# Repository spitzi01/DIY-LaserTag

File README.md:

# ESP32-LaserTag
Easy Open Source LaserTag System
### Überblick
Ziel dieses Projektes war der Bau eines einfachen LaserTag-Systems. Es sollte schnell und mit wenig Hardware an beliebigen Orten aufbaubar sein und  und über ein Handy gesteuert werden können.

Weitere Features sind:

- Soundausgabe für Schuss, Treffer und Nachladen (insgesamt 5 Verschiedene)
- Display in jedem Tagger
- lange Akkulaufzeit des gesamten Systems
- 3 Spielmodi
- Taschenlampe
- rote Laserdiode für Schuss-Simulation
- 5 in den Tagger integriete Infrarot-Empfänger
    
Das LaserTag-System besteht aus zwei elementaren Bestandteilen. Die Basisstation dient als Verbindungsglied zwischen den Taggern, der einzelnen Spieler, und einer HTTP-Website, welche der Konfiguration und Auswertung dient. Der Datenaustausch mit den Spielern erfolgt drahtlos mit Hilfe des EspNow-Protokolls der ESP32 S2 Mikrocontroller. Zum Spielen sind zwischen 2 und 10 Tagger notwendig. Für den Capture the Flag Spielmodus werden zusätzlich noch Flags benötigt, die die Basis und Spawnpunkt eines Team markieren.

### Basisstation

Nach dem Einschalten der Basisstation wird ein WLAN-Netzwerk erzeugt und die Konfigurationswebsite gehostet. Wenn man sich hier mit einem Smartphone einloggt, kann man die Anzahl der Spieler, Dauer des Spiels, Modus, Namen der Spieler und Teamzugehörigkeit einstellen. Die maximal 10 Spieler können auf 6 Teams verteilt werden. Vor dem Starten des Spiels mit dem Start-Taster müssen unbedingt alle Tagger, die verwendet werden sollen, eingeschaltet werden, damit diese von der Basisstation ihre Informationen erhalten können. Nach Ablauf der Spieldauer übermitteln die Tagger automatisch die Spielstände an die Basisstation und schalten sich ab. Die Basisstation berechnet die Ergebnisse und hostet diese in Form einer Website. Das hat den Vorteil, dass sich theoretisch mehrere Spieler die Ergebnisse auf ihren Smartphones anschauen können.

### Tagger

Bei einem Testsystem wurde festgestellt, dass es dem Spieler nicht möglich sein darf, seinen Tagger aus Versehen auszuschalten. Deshalb wird die Schaltung durch einen Taster aktiviert und nur durch den Mikrocontroller wieder deaktiviert. Außerdem soll der Spieler immer beide Hände am Tagger haben. So soll verhindert werden, dass man mit einer Hand Sensoren abdecken könnte. Dies wird durch einen Taster in Reihe zum eigentlichen Abzug realisiert. Gleichzeitig schaltet dieser auch die Taschenlampe an. In meinem Fall dient ein kleiner 12V Bleiakku aus einer Brandmeldezentrale als Energieversorgung. Mit Hilfe des Step Down Converters wird eine hohe Effizienz und Akkulaufzeit erreicht. Das Display hat 20 alphanumerische Stellen, welche die Namen der Spieler und die Anzahl der Leben anzeigen. Eine Hintergrundbeleuchtung ist nicht vorhanden, da diese zu viel Strom benötigen würde. Deshalb dient die RGB-LED für die Teamzugehörigkeit als Beleuchtung. Edit: Mittlerweile wurde das Display durch ein OLED 0,96" Display getauscht, da das LCD Display nicht mehr verfügbar war. Ebenso wurde der Akku durch einen günstigen 12V Lithium-Ionen Akku ersetzt.

Der Schuss wird durch eine Laserdiode visualisiert. Die eigentliche Information findet durch eine IR-Übertragung ihren Weg zu anderen Spielern. Bei Tests in der Nacht konnte eine Reichweite von bis zu 60 Meter erzielt werden. Der kurze Alu-Lauf dient als Reflektor für die Infrarot-LED und auch als Kühlkörper, da bei aktiviertem Schnellfeuermodus die LED sehr belastet wird.

Die verfügbaren Spielmodi sind:

- Standard (Spielen in Teams oder Einzeln, Reaktivierung nach ca. 20 Sekunden)
- Battle Royal (Spielen in Teams oder Einzeln, Leben werden bei Treffer weniger, kein Treffer in gewisser Zeit fügt ein Leben hinzu, lange Reaktivierungszeit ca. 2 Minuten)
- Capture the Flag (2 Teams rot & blau, Flags markieren Basis oder Spawnpunkt des jeweiligen Teams, Reaktivierung nur im Bereich des eigenen Spawnpunkts, Punkte bei Aufenthalt in gegnerischen Basis)

### Flag
Ein Flag sendet in regelmäßigen Abständen einen Code der von den Taggern empfangen wird. Bereich, in dem das Signal empfangbar ist, beträgt in etwa 5-8 Meter im Radius. Diese Strecke ergibt sich durch den Einsatz von ESP32 S2 Mikrocontroller ohne integriete Antenne in den Taggern.

### Verbesserungsmöglichkeiten

- Reichweite bei starkem Sonnenschein eingeschränkt
- Mikrocontroller überträgt kurzes Störgeräusch über I2S nach Ende einer Soundausgabe (Software Problem)
- Skalierbarkeit (mehr als 10 Spieler)

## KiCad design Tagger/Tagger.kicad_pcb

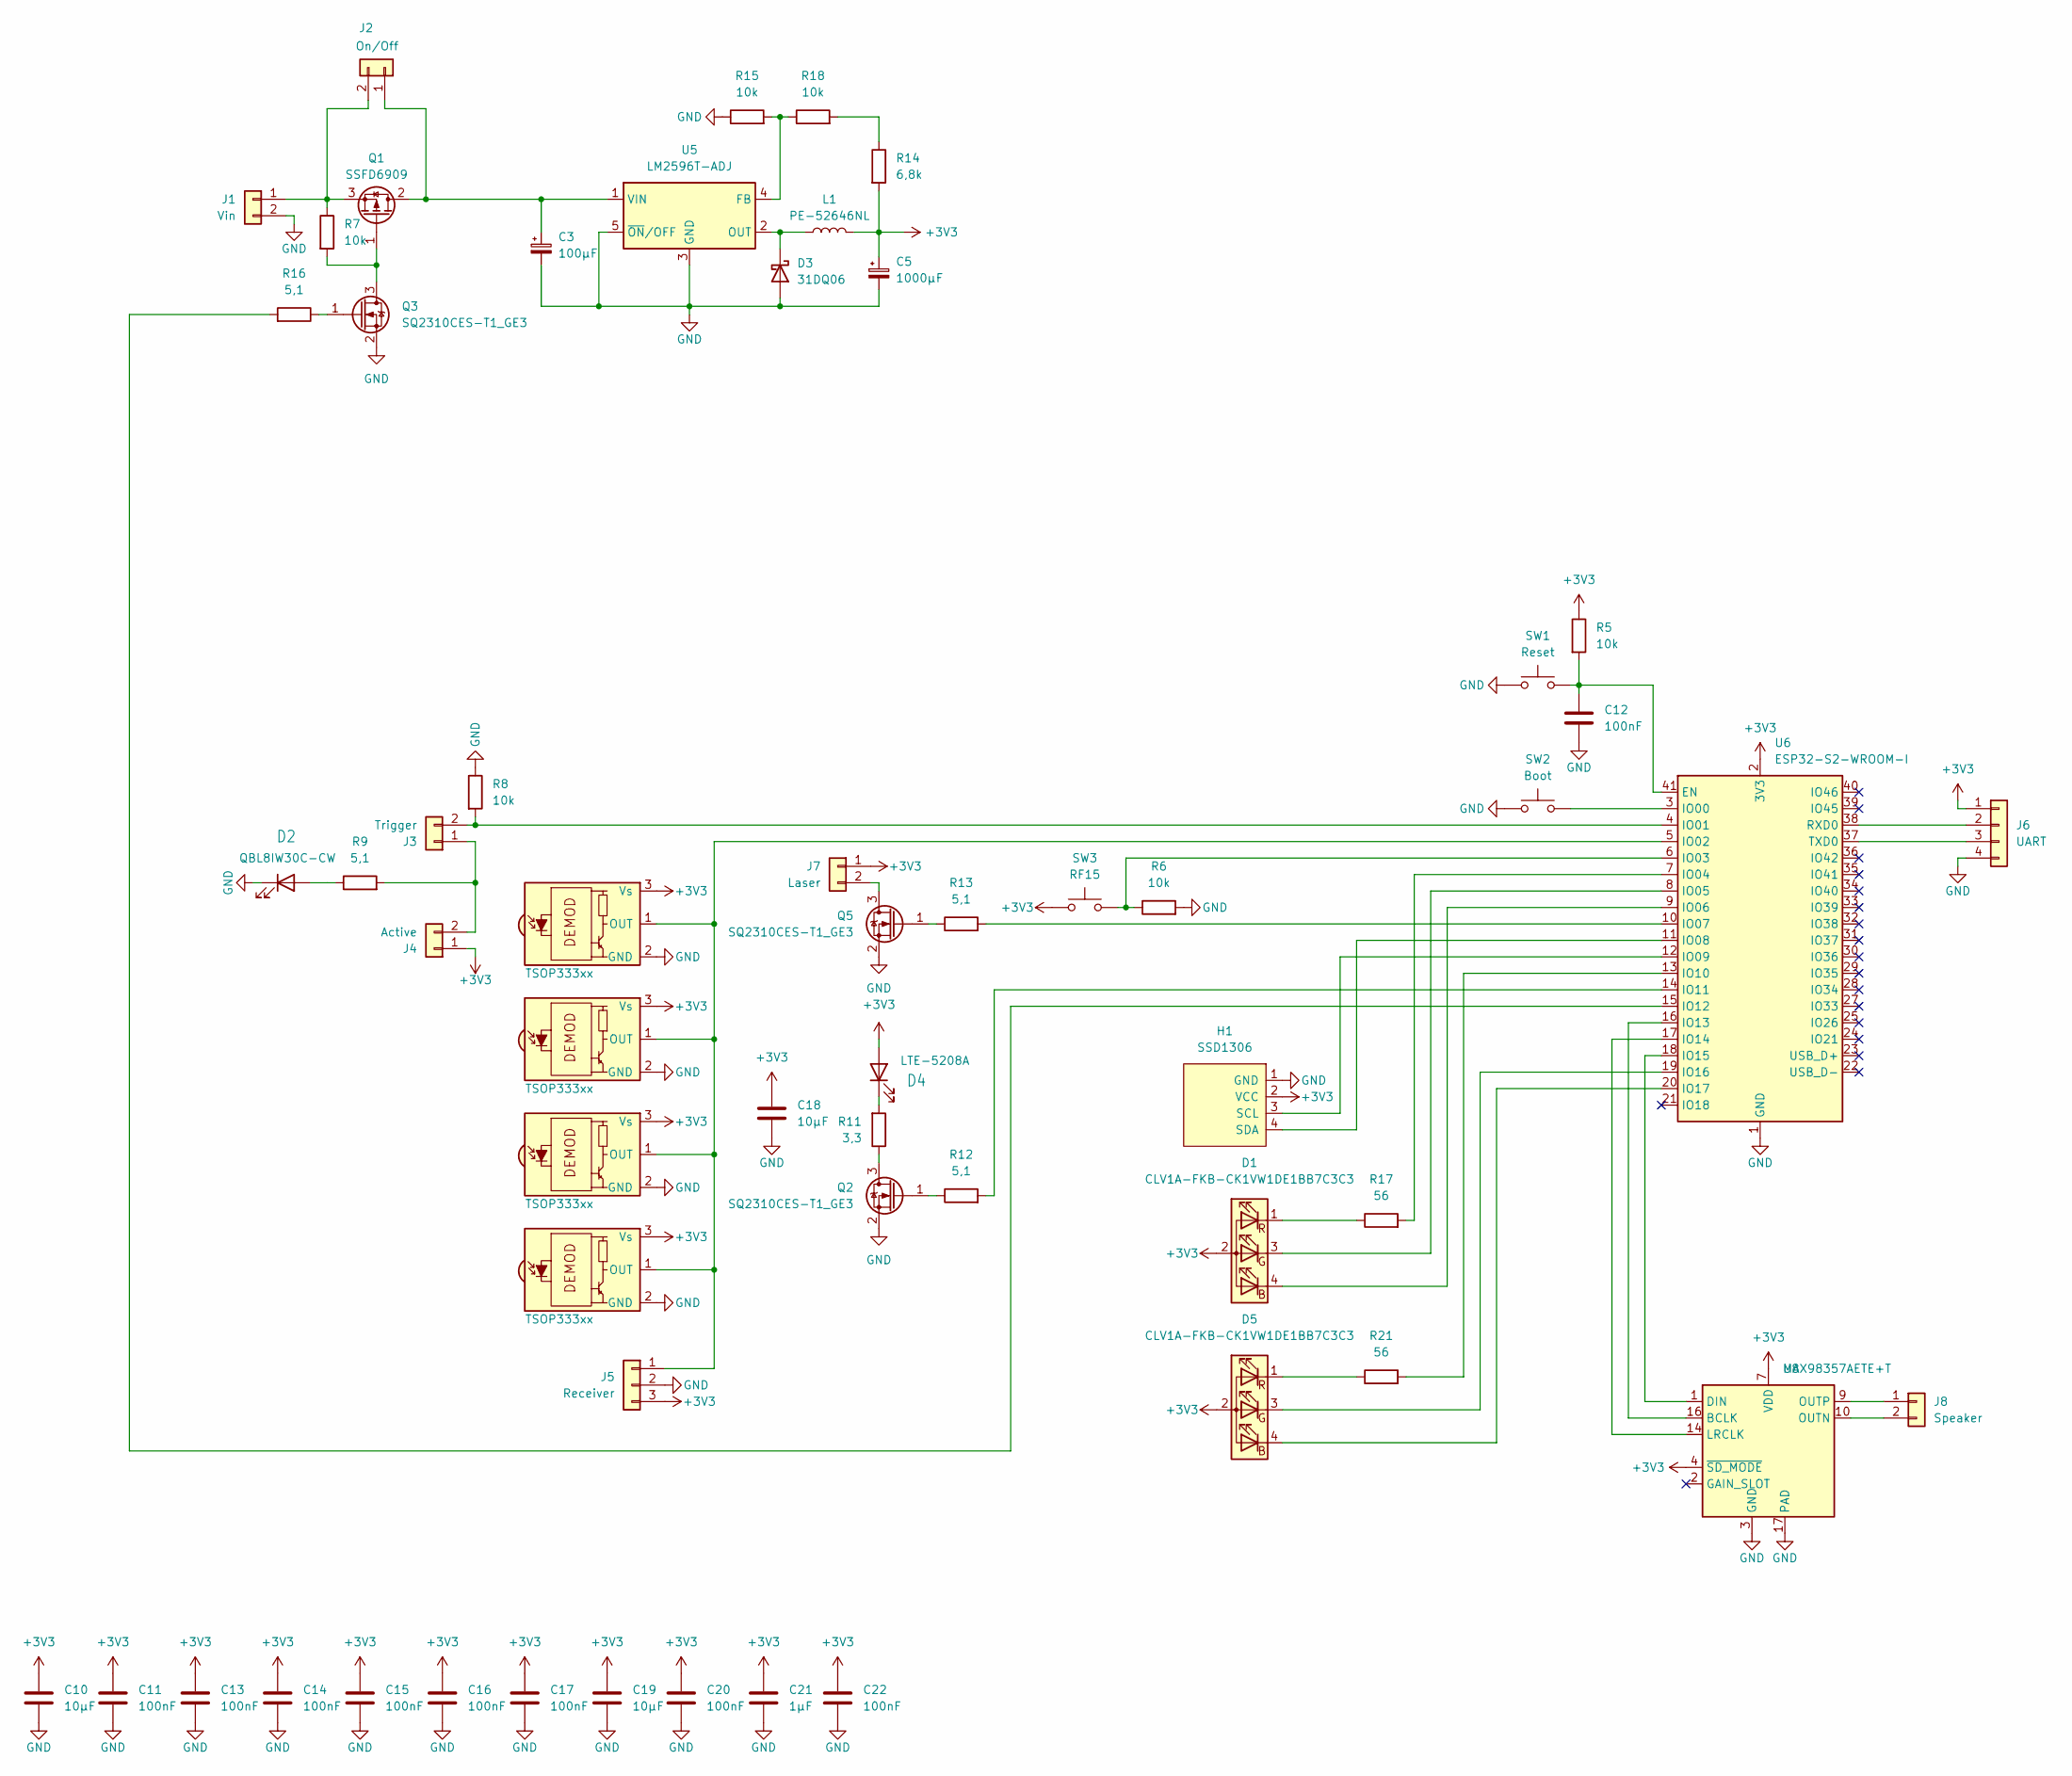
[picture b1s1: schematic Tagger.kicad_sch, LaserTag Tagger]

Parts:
C3: 100µF; CP_Radial_D6.3mm_P2.50mm
C5: 1000µF; CP_Radial_D10.0mm_P5.00mm
C10, C18, C19: 10µF; C_1206_3216Metric
C11, C12, C13, C14, C15, C16, C17, C20, C22: 100nF; C_0805_2012Metric
C21: 1µF; C_0805_2012Metric
D1, D5: CLV1A-FKB-CK1VW1DE1BB7C3C3; LED_Cree-PLCC4_3.2x2.8mm_CCW
D2: QBL8IW30C-CW; LED_D5.0mm_Clear
D3: 31DQ06; D_DO-201AD_P15.24mm_Horizontal
D4: LTE-5208A; LED_D5.0mm_Clear
H1: SSD1306; 128x64OLED
J1: Vin; MKDSN1,5_2-5,08
J2: On/Off; MKDSN1,5_2-5,08
J3: Trigger; MKDSN1,5_2-5,08
J4: Active; MKDSN1,5_2-5,08
J5: Receiver; PinHeader_1x03_P2.54mm_Vertical
J6: UART; PinHeader_1x04_P2.54mm_Vertical
J7: Laser; PinHeader_1x02_P2.54mm_Vertical
J8: Speaker; PinHeader_1x02_P2.54mm_Vertical
L1: PE-52646NL; PE52646
Q1: SSFD6909; TO-252-2
Q2, Q3, Q5: SQ2310CES-T1_GE3; SOT-23
R5, R6, R7, R8: 10k; R_0805_2012Metric
R9, R12, R13, R16: 5,1; R_0805_2012Metric
R11: 3,3; R_0805_2012Metric
R14: 6,8k; R_1206_3216Metric
R15, R18: 10k; R_1206_3216Metric
R17, R21: 56; R_0805_2012Metric
SW1: Reset; SW_SPST_TL3305C
SW2: Boot; SW_SPST_TL3305C
SW3: RF15
U1, U2, U3, U4: TSOP333xx; Vishay_MINIMOLD-3Pin
U5: LM2596T-ADJ; TO-220-5_P3.4x3.8mm_StaggerOdd_Lead7.13mm_TabDown
U6: ESP32-S2-WROOM-I; ESP32-S2-WROVER
U8: MAX98357AETE+T; TQFN-16-1EP_3x3mm_P0.5mm_EP1.23x1.23mm

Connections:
+3V3: C5.1, C10.1, C11.1, C13.1, C14.1, C15.1, C16.1, C17.1, C18.1, C19.1, C20.1, C21.1, C22.1, D1.2 (A), D4.2 (A), D5.2 (A), H1.2 (VCC), J4.1, J5.3, J6.1, J7.1, L1.2, R5.1, R14.2, SW3.2, U1.3 (Vs), U2.3 (Vs), U3.3 (Vs), U4.3 (Vs), U6.2 (3V3), U8.4 (~SD_MODE), U8.7 (VDD), U8.8 (VDD)
GND: C3.2, C5.2, C10.2, C11.2, C12.1, C13.2, C14.2, C15.2, C16.2, C17.2, C18.2, C19.2, C20.2, C21.2, C22.2, D2.1 (K), D3.2 (A), H1.1 (GND), J1.2, J5.2, J6.4, Q2.2 (S), Q3.2 (S), Q5.2 (S), R6.2, R8.1, R15.1, SW1.1, SW2.1, U1.2 (GND), U2.2 (GND), U3.2 (GND), U4.2 (GND), U5.3 (GND), U5.5 (~ON/OFF), U6.1 (GND), U6.26 (GND), U6.42 (GND), U6.43 (GND), U8.3 (GND), U8.11 (GND), U8.15 (GND), U8.17 (PAD)
unnamed: D1.4 (BK), U6.9 (IO06)
unnamed: D1.3 (GK), U6.8 (IO05)
unnamed: D1.1 (RK), R17.1
unnamed: D2.2 (A), R9.1
unnamed: D3.1 (K), L1.1, U5.2 (OUT)
unnamed: D4.1 (K), R11.2
unnamed: D5.4 (BK), U6.20 (IO17)
unnamed: D5.3 (GK), U6.19 (IO16)
unnamed: D5.1 (RK), R21.1
unnamed: H1.3 (SCL), U6.12 (IO09)
unnamed: H1.4 (SDA), U6.11 (IO08)
unnamed: J1.1, J2.2, Q1.3 (S), R7.1
unnamed: C3.1, J2.1, Q1.2 (D), U5.1 (VIN)
unnamed: J3.1, J4.2, R9.2
unnamed: J3.2, R8.2, U6.4 (IO01)
unnamed: J5.1, U1.1 (OUT), U2.1 (OUT), U3.1 (OUT), U4.1 (OUT), U6.5 (IO02)
unnamed: J6.2, U6.38 (RXD0)
unnamed: J6.3, U6.37 (TXD0)
unnamed: J7.2, Q5.3 (D)
unnamed: J8.1, U8.9 (OUTP)
unnamed: J8.2, U8.10 (OUTN)
unnamed: Q1.1 (G), Q3.3 (D), R7.2
unnamed: Q2.3 (D), R11.1
unnamed: Q2.1 (G), R12.1
unnamed: Q3.1 (G), R16.1
unnamed: Q5.1 (G), R13.1
unnamed: R14.1, R18.2
unnamed: R15.2, R18.1, U5.4 (FB)
unnamed: C12.2, R5.2, SW1.2, U6.41 (EN)
unnamed: SW2.2, U6.3 (IO00)
unnamed: R6.1, SW3.1, U6.6 (IO03)
unnamed: R17.2, U6.7 (IO04)
unnamed: R13.2, U6.10 (IO07)
unnamed: R21.2, U6.13 (IO10)
unnamed: R12.2, U6.14 (IO11)
unnamed: R16.2, U6.15 (IO12)
unnamed: U6.16 (IO13), U8.16 (BCLK)
unnamed: U6.17 (IO14), U8.14 (LRCLK)
unnamed: U6.18 (IO15), U8.1 (DIN)

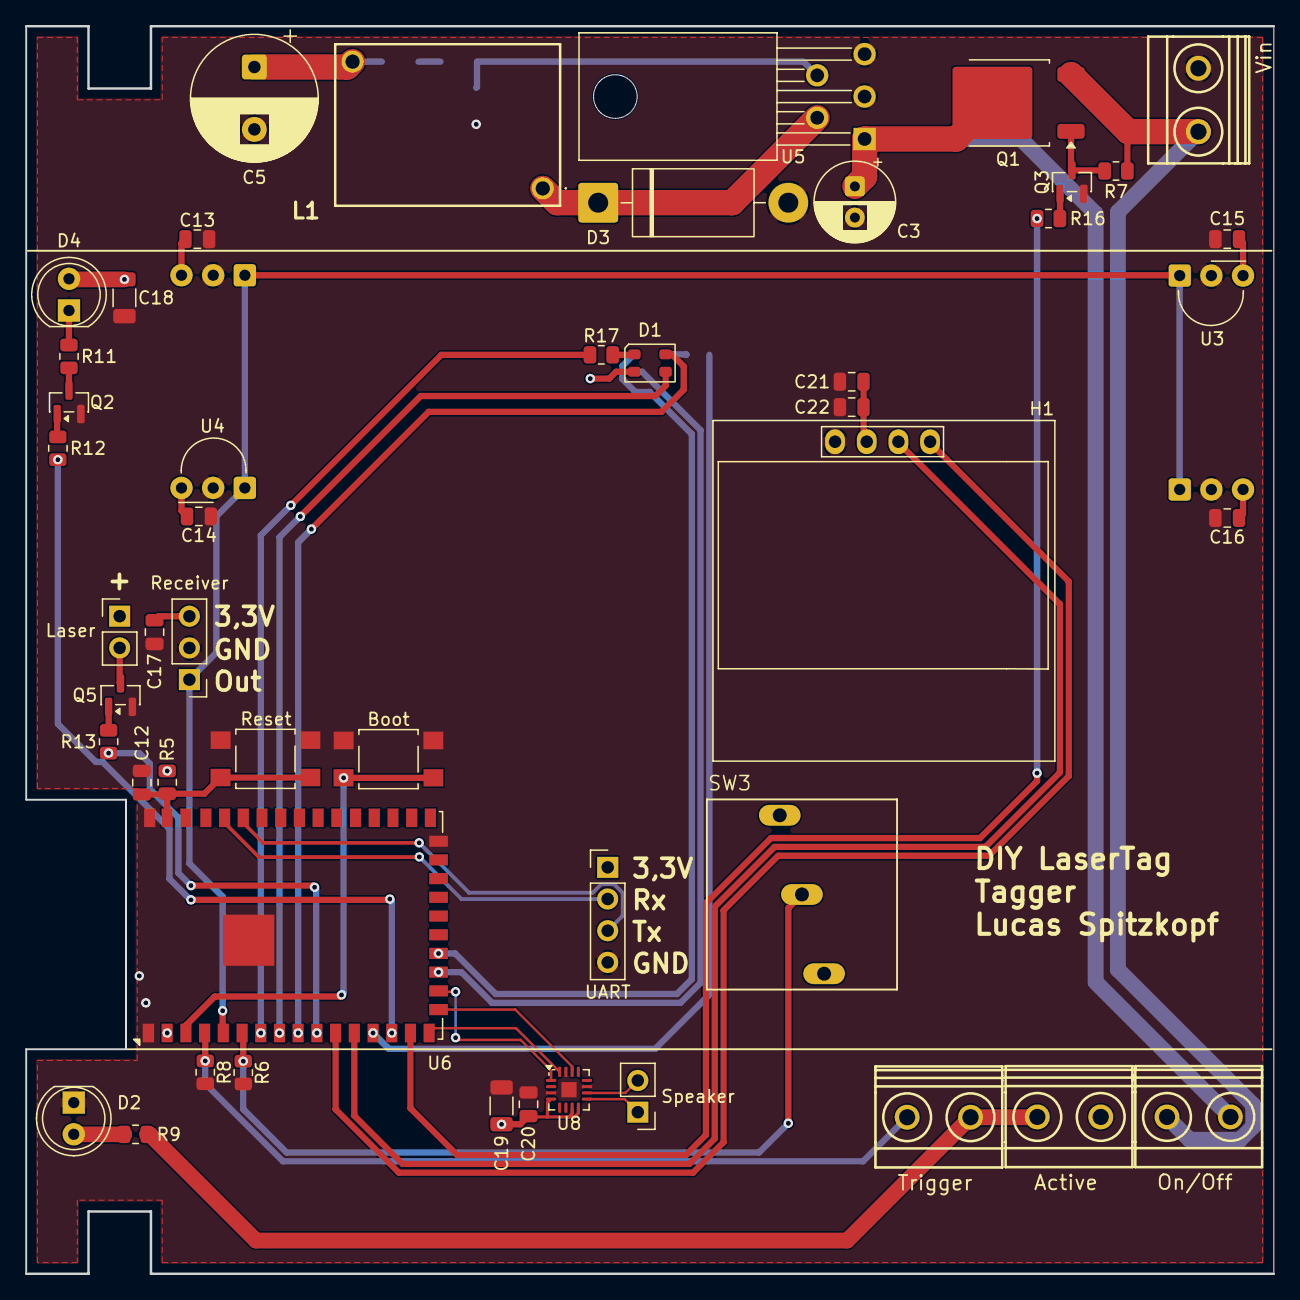
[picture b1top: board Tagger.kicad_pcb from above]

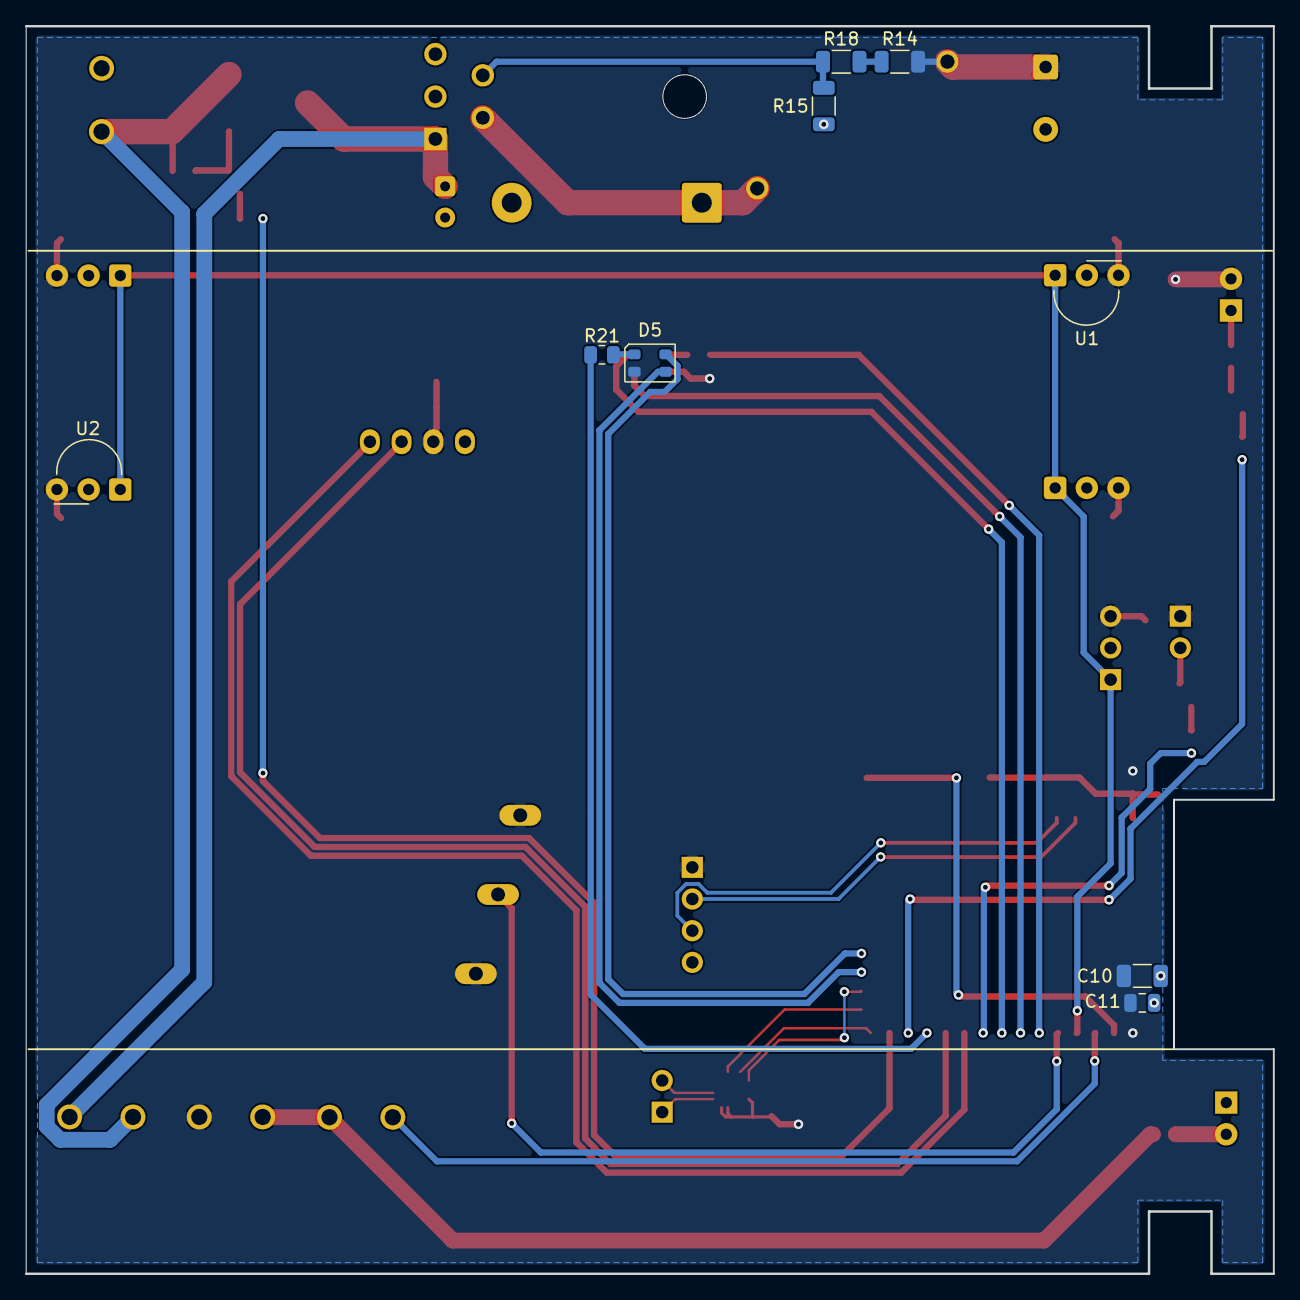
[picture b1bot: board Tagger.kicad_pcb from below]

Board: 2 copper layers, 100.0 x 100.0 mm, 58 parts (9 on the bottom side), 41 nets.

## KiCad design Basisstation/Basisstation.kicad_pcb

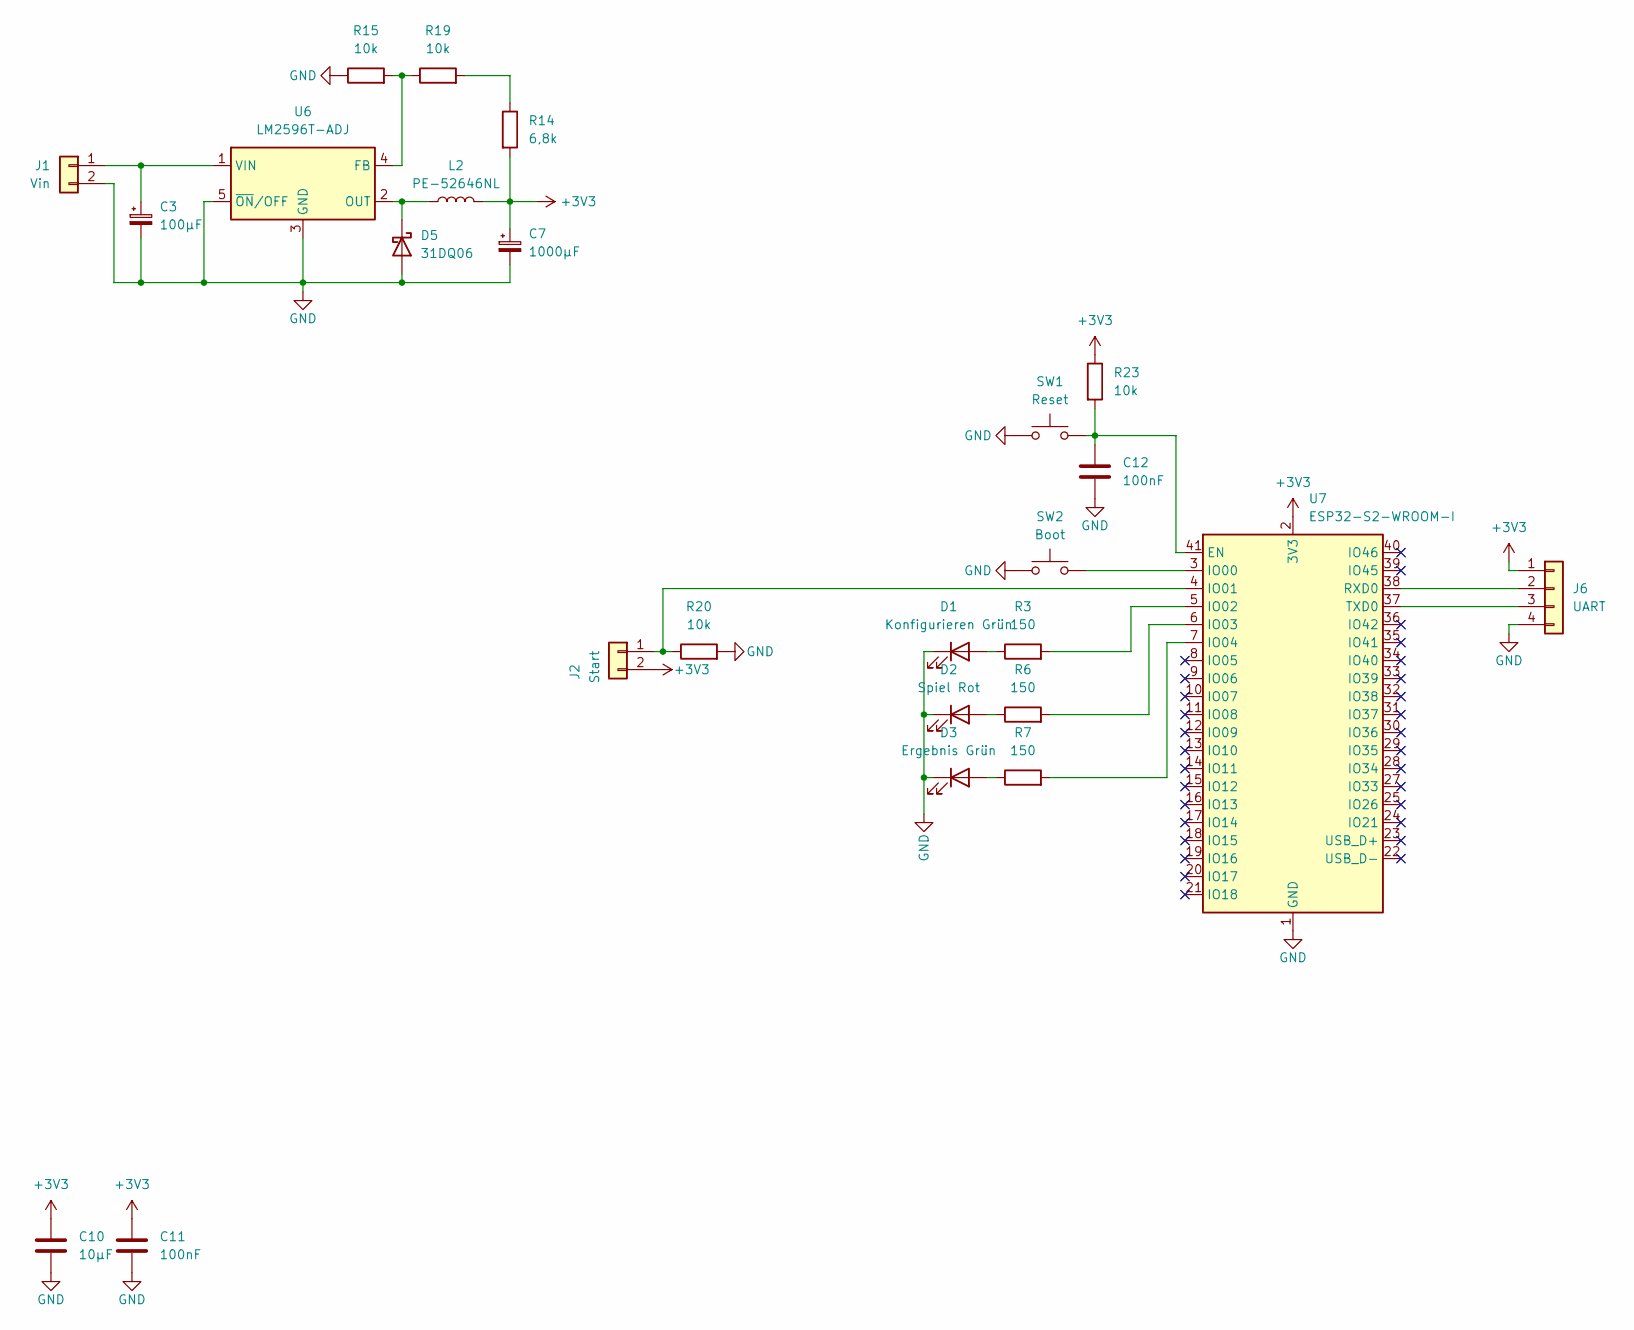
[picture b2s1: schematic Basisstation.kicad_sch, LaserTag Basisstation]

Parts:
C3: 100µF; CP_Radial_D6.3mm_P2.50mm
C7: 1000µF; CP_Radial_D10.0mm_P5.00mm
C10: 10µF; C_1206_3216Metric
C11, C12: 100nF; C_0805_2012Metric
D1: Konfigurieren Grün; LED_D5.0mm
D2: Spiel Rot; LED_D5.0mm
D3: Ergebnis Grün; LED_D5.0mm
D5: 31DQ06; D_DO-201AD_P15.24mm_Horizontal
J1: Vin; MKDSN1,5_2-5,08
J2: Start; MKDSN1,5_2-5,08
J6: UART; PinHeader_1x04_P2.54mm_Vertical
L2: PE-52646NL; PE52646
R3, R6, R7: 150; R_0805_2012Metric
R14: 6,8k; R_1206_3216Metric
R15, R19: 10k; R_1206_3216Metric
R20, R23: 10k; R_0805_2012Metric
SW1: Reset; SW_SPST_TL3305C
SW2: Boot; SW_SPST_TL3305C
U6: LM2596T-ADJ; TO-220-5_P3.4x3.8mm_StaggerOdd_Lead7.13mm_TabDown
U7: ESP32-S2-WROOM-I; ESP32-S2-WROVER

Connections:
+3V3: C7.1, C10.1, C11.1, J2.2, J6.1, L2.2, R14.2, R23.1, U7.2 (3V3)
GND: C3.2, C7.2, C10.2, C11.2, C12.1, D1.1 (K), D2.1 (K), D3.1 (K), D5.2 (A), J1.2, J6.4, R15.1, R20.2, SW1.1, SW2.1, U6.3 (GND), U6.5 (~ON/OFF), U7.1 (GND), U7.26 (GND), U7.42 (GND), U7.43 (GND)
unnamed: D1.2 (A), R3.1
unnamed: D2.2 (A), R6.1
unnamed: D3.2 (A), R7.1
unnamed: D5.1 (K), L2.1, U6.2 (OUT)
unnamed: C3.1, J1.1, U6.1 (VIN)
unnamed: J2.1, R20.1, U7.4 (IO01)
unnamed: J6.2, U7.38 (RXD0)
unnamed: J6.3, U7.37 (TXD0)
unnamed: R14.1, R19.2
unnamed: R15.2, R19.1, U6.4 (FB)
unnamed: C12.2, R23.2, SW1.2, U7.41 (EN)
unnamed: SW2.2, U7.3 (IO00)
unnamed: R3.2, U7.5 (IO02)
unnamed: R6.2, U7.6 (IO03)
unnamed: R7.2, U7.7 (IO04)

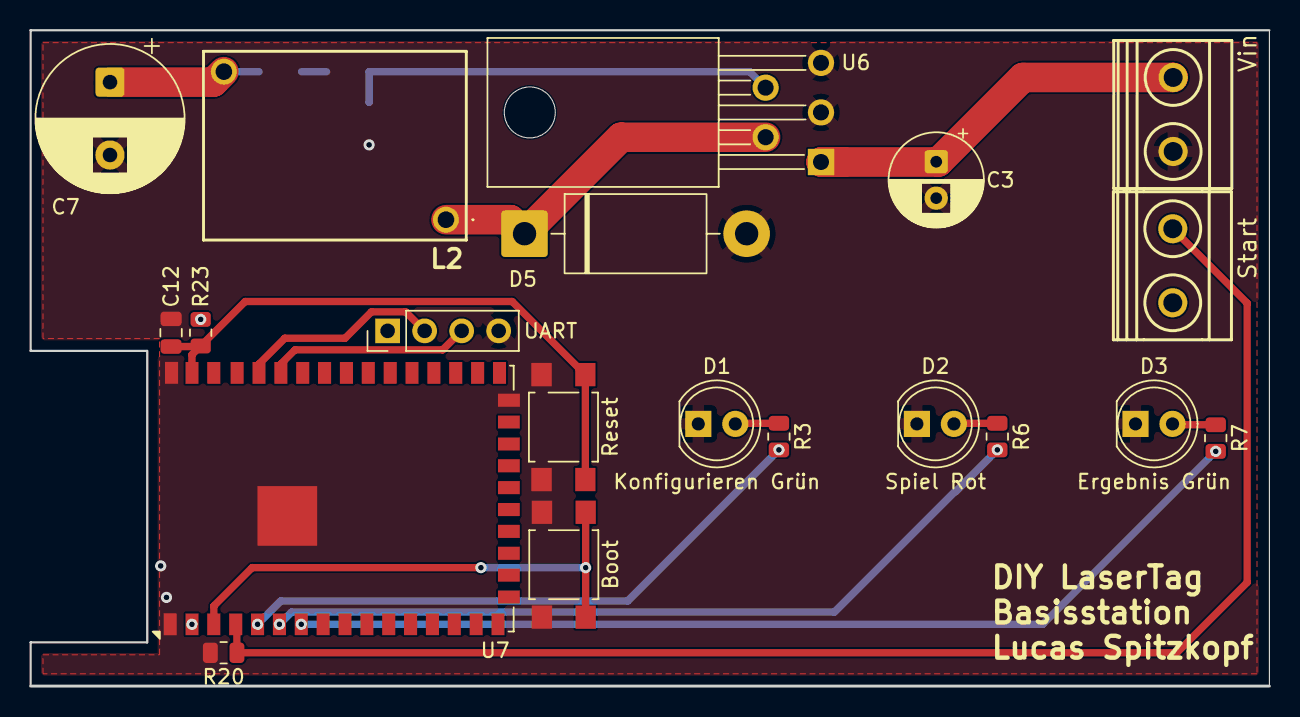
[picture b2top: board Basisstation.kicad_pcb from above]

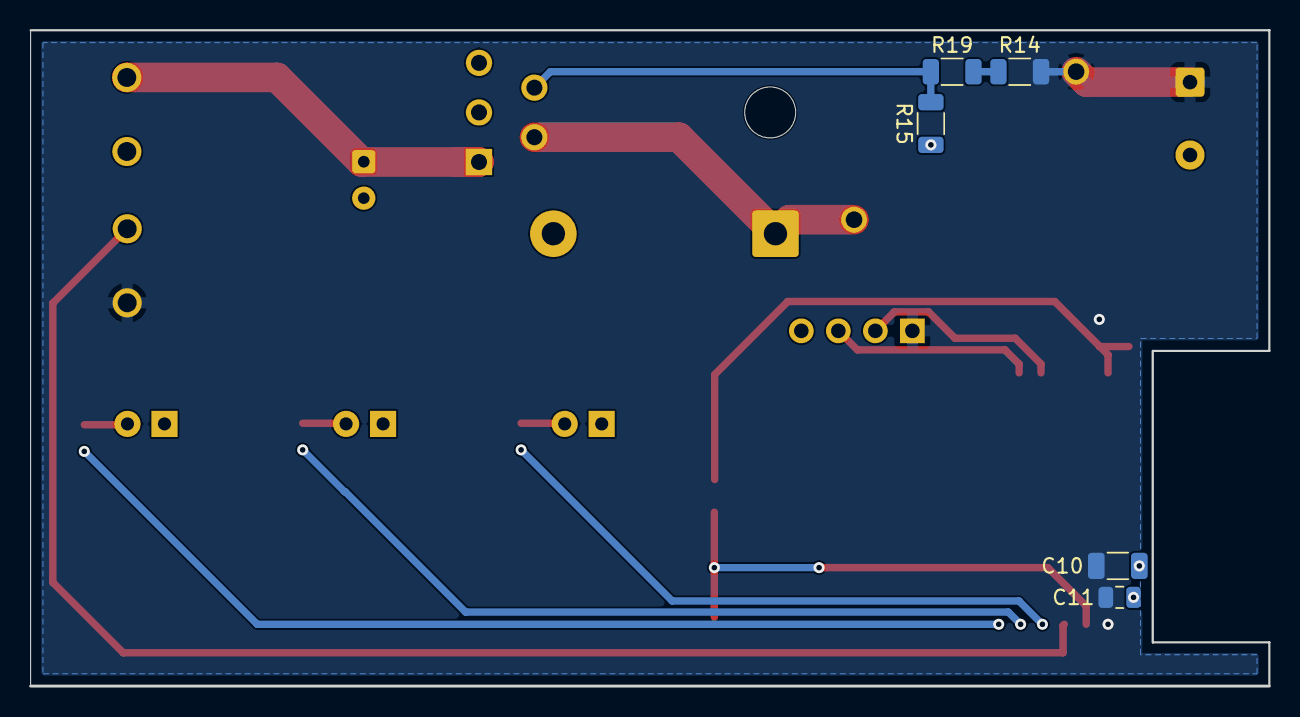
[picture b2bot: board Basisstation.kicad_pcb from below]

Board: 2 copper layers, 85.0 x 45.0 mm, 25 parts (5 on the bottom side), 17 nets.

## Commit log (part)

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2022-03-29 Create LICENSE
2022-09-05 Rename LaserTag1.ino to Tagger1.ino
2022-09-05 Rename LaserTag2.ino to Tagger2.ino
2022-09-05 Rename LaserTag10.ino to Tagger10.ino
2022-09-05 Rename LaserTag3.ino to Tagger3.ino
2022-09-05 Rename LaserTag4.ino to Tagger4.ino
2022-09-05 Rename LaserTag5.ino to Tagger5.ino
2022-09-05 Rename LaserTag6.ino to Tagger6.ino
2022-09-05 Rename LaserTag7.ino to Tagger7.ino
2022-09-05 Rename LaserTag8.ino to Tagger8.ino
2022-09-05 Rename LaserTag9.ino to Tagger9.ino
